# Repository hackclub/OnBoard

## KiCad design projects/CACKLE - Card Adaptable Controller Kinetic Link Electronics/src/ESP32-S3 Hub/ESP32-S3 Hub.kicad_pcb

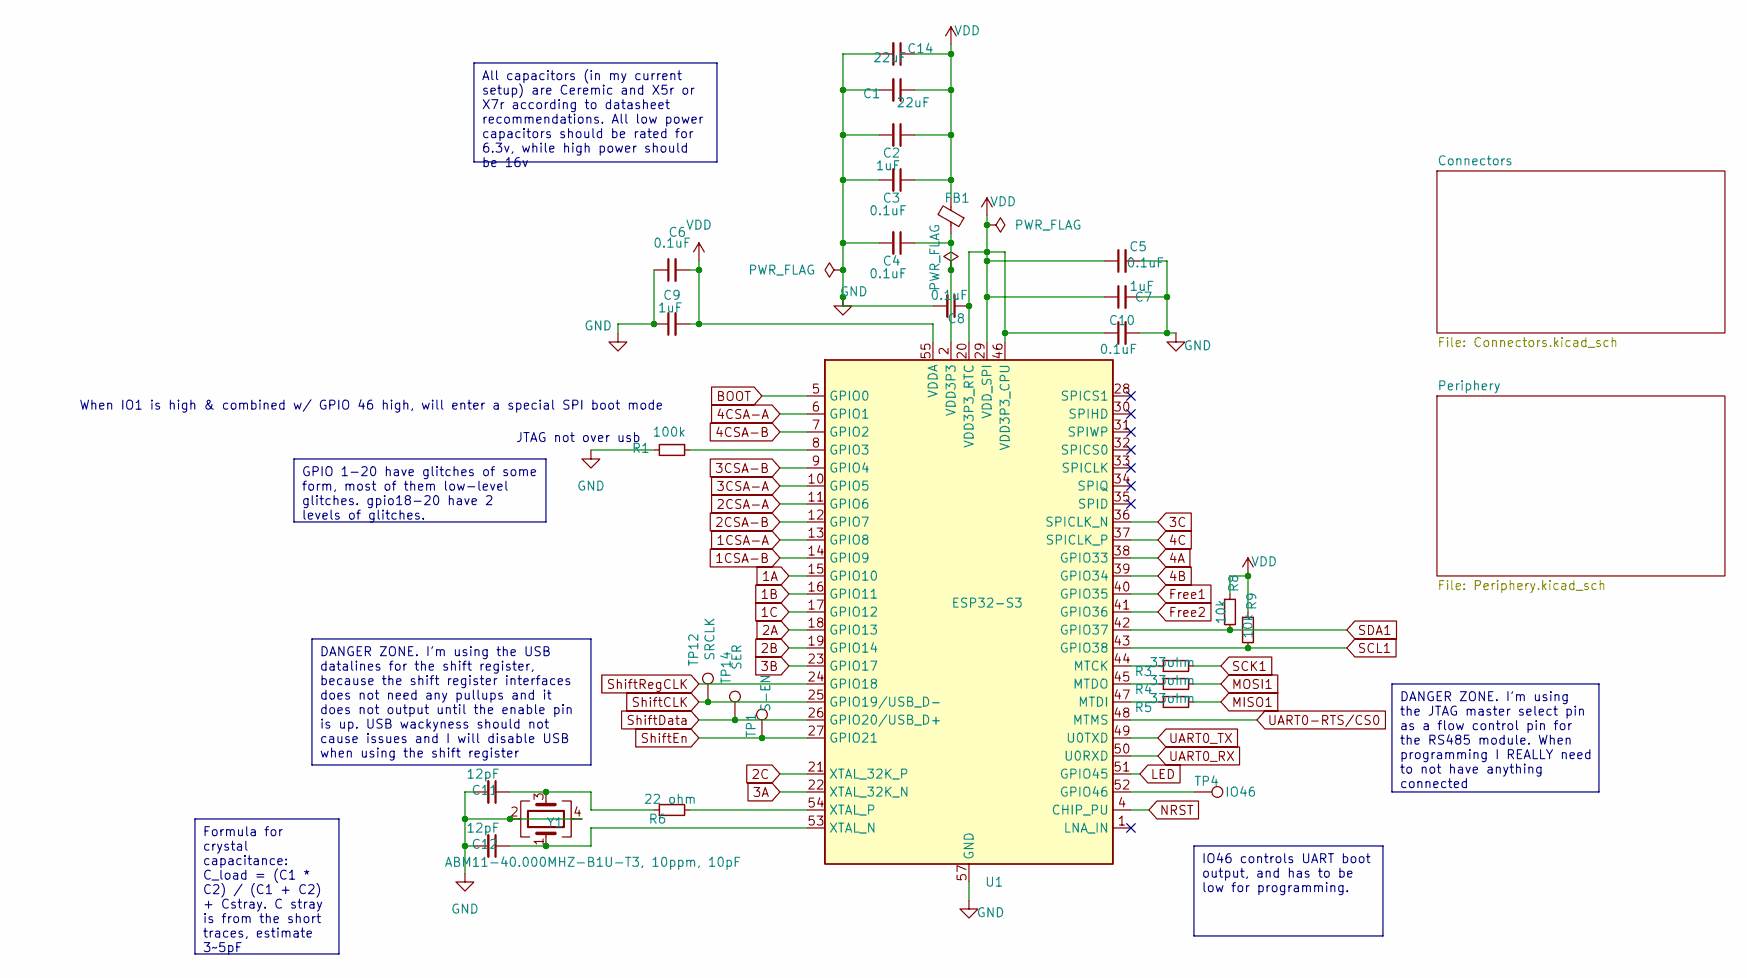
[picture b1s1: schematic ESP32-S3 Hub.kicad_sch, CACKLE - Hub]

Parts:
C1, C14: 22uF; C_0402_1005Metric; LCSC C415703
C2, C7, C9: 1uF; C_0402_1005Metric; LCSC C52923
C3, C4, C5, C6, C8, C10: 0.1uF; C_0402_1005Metric; LCSC C1525
C11, C12: 12pF; C_0402_1005Metric; LCSC C1547
FB1: 120ohm imp @100mhz, 1 amp; L_0402_1005Metric; LCSC C82861
R1: 100k; R_0402_1005Metric; LCSC C25741
R3, R4, R5: 33ohm; R_0402_1005Metric; LCSC C25105
R6: 22 ohm; R_0402_1005Metric; LCSC C25092
R8, R9: 10k; R_0402_1005Metric; LCSC C25744
TP1: S-EN; TestPoint_Pad_D1.0mm
TP4: IO46; TestPoint_Pad_D1.0mm
TP12: SRCLK; TestPoint_Pad_D1.0mm
TP14: SER; TestPoint_Pad_D1.0mm
U1: ESP32-S3; QFN-56-1EP_7x7mm_P0.4mm_EP4x4mm; LCSC C3013940
Y1: ABM11-40.000MHZ-B1U-T3, 10ppm, 10pF; Crystal_SMD_2016-4Pin_2.0x1.6mm; LCSC C648973

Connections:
1A: U1.15 (GPIO10); also elsewhere on the board
1B: U1.16 (GPIO11); also elsewhere on the board
1C: U1.17 (GPIO12); also elsewhere on the board
1CSA-A: U1.13 (GPIO8); also elsewhere on the board
1CSA-B: U1.14 (GPIO9); also elsewhere on the board
2A: U1.18 (GPIO13); also elsewhere on the board
2B: U1.19 (GPIO14); also elsewhere on the board
2C: U1.21 (XTAL_32K_P); also elsewhere on the board
2CSA-A: U1.11 (GPIO6); also elsewhere on the board
2CSA-B: U1.12 (GPIO7); also elsewhere on the board
3A: U1.22 (XTAL_32K_N); also elsewhere on the board
3B: U1.23 (GPIO17); also elsewhere on the board
3C: U1.36 (SPICLK_N); also elsewhere on the board
3CSA-A: U1.10 (GPIO5); also elsewhere on the board
3CSA-B: U1.9 (GPIO4); also elsewhere on the board
4A: U1.38 (GPIO33); also elsewhere on the board
4B: U1.39 (GPIO34); also elsewhere on the board
4C: U1.37 (SPICLK_P); also elsewhere on the board
4CSA-A: U1.6 (GPIO1); also elsewhere on the board
4CSA-B: U1.7 (GPIO2); also elsewhere on the board
BOOT: U1.5 (GPIO0); also elsewhere on the board
Free1: U1.40 (GPIO35); also elsewhere on the board
Free2: U1.41 (GPIO36); also elsewhere on the board
GND: C1.2, C2.2, C3.2, C4.2, C5.2, C6.1, C7.2, C8.2, C9.1, C10.2, C11.2, C12.2, C14.2, R1.2, U1.57 (GND), Y1.2, Y1.4; also elsewhere on the board
LED: U1.51 (GPIO45); also elsewhere on the board
MISO1: R5.2; also elsewhere on the board
MOSI1: R4.2; also elsewhere on the board
NRST: U1.4 (CHIP_PU); also elsewhere on the board
unnamed: C4.1, FB1.1, U1.2 (VDD3P3), U1.3 (VDD3P3)
unnamed: C11.1, R6.1, Y1.3
unnamed: R1.1, U1.8 (GPIO3)
unnamed: TP4.1, U1.52 (GPIO46)
unnamed: R3.1, U1.44 (MTCK)
unnamed: R5.1, U1.47 (MTDI)
unnamed: R4.1, U1.45 (MTDO)
unnamed: C12.1, U1.53 (XTAL_N), Y1.1
unnamed: R6.2, U1.54 (XTAL_P)
SCK1: R3.2; also elsewhere on the board
SCL1: R9.2, U1.43 (GPIO38); also elsewhere on the board
SDA1: R8.2, U1.42 (GPIO37); also elsewhere on the board
ShiftCLK: TP12.1, U1.25 (GPIO19/USB_D-); also elsewhere on the board
ShiftData: TP14.1, U1.26 (GPIO20/USB_D+); also elsewhere on the board
ShiftEn: TP1.1, U1.27 (GPIO21); also elsewhere on the board
ShiftRegCLK: U1.24 (GPIO18); also elsewhere on the board
UART0-RTS/CS0: U1.48 (MTMS); also elsewhere on the board
UART0_RX: U1.50 (U0RXD); also elsewhere on the board
UART0_TX: U1.49 (U0TXD); also elsewhere on the board
VDD: C1.1, C2.1, C3.1, C5.1, C6.2, C7.1, C8.1, C9.2, C10.1, C14.1, FB1.2, R8.1, R9.1, U1.20 (VDD3P3_RTC), U1.29 (VDD_SPI), U1.46 (VDD3P3_CPU), U1.55 (VDDA), U1.56 (VDDA); also elsewhere on the board

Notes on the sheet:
DANGER ZONE. I'm using the JTAG master select pin as a flow control pin for the RS485 module. When programming I REALLY need to not have anything connected
DANGER ZONE. I'm using the USB datalines for the shift register, because the shift register interfaces does not need any pullups and it does not output until the enable pin is up. USB wackyness should not cause issues and I will disable USB when using the shift register
All capacitors (in my current setup) are Ceremic and X5r or X7r according to datasheet recommendations. All low power capacitors should be rated for 6.3v, while high power should be 16v
IO46 controls UART boot output, and has to be low for programming.
GPIO 1-20 have glitches of some form, most of them low-level glitches. gpio18-20 have 2 levels of glitches.
Formula for crystal capacitance: C_load = (C1 * C2) / (C1 + C2) + Cstray. C stray is from the short traces, estimate 3~5pF
JTAG not over usb
When IO1 is high & combined w/ GPIO 46 high, will enter a special SPI boot mode

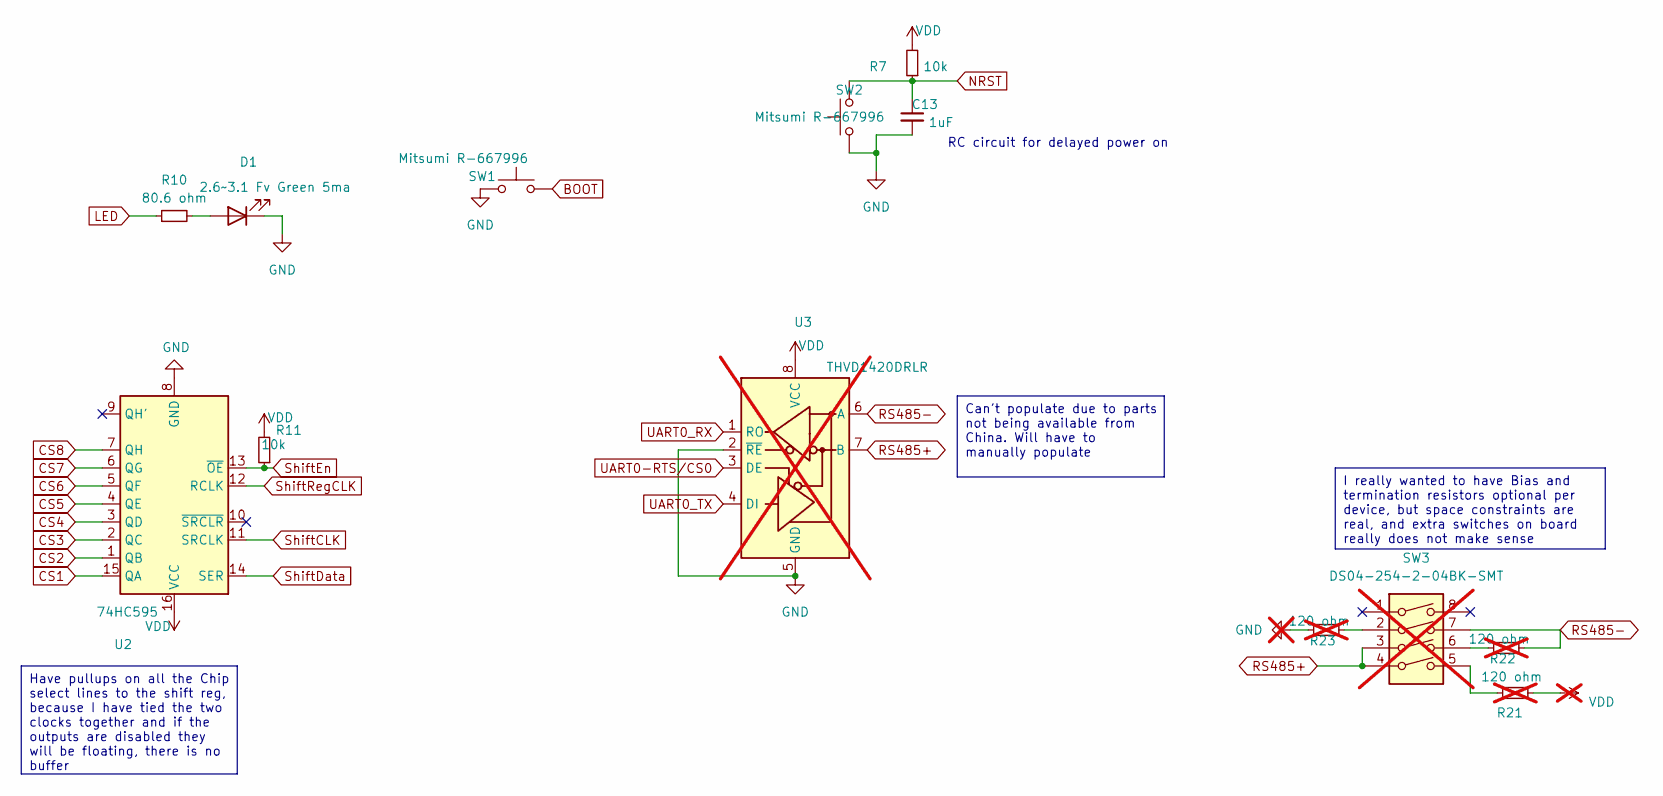
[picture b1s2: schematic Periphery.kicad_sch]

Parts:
C13: 1uF; C_0402_1005Metric; LCSC C52923
D1: 2.6~3.1 Fv Green 5ma; LED_0603_1608Metric_Pad1.05x0.95mm_HandSolder; LCSC C3028858
R7, R11: 10k; R_0402_1005Metric; LCSC C25744
R10: 80.6 ohm; R_0402_1005Metric; LCSC C185392
R21, R22, R23: 120 ohm; R_0402_1005Metric; not fitted
SW1, SW2: Mitsumi R-667996; R-667995_MIT; LCSC C4365007
SW3: DS04-254-2-04BK-SMT; SW_DIP_SPSTx04_Slide_Omron_A6S-410x_W8.9mm_P2.54mm; not fitted
U2: 74HC595; DHVQFN-16-1EP_2.5x3.5mm_P0.5mm_EP1x2mm; LCSC C730243
U3: THVD1420DRLR; SOT-583-8; not fitted

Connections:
BOOT: SW1.2; also elsewhere on the board
CS1: U2.15 (QA); also elsewhere on the board
CS2: U2.1 (QB); also elsewhere on the board
CS3: U2.2 (QC); also elsewhere on the board
CS4: U2.3 (QD); also elsewhere on the board
CS5: U2.4 (QE); also elsewhere on the board
CS6: U2.5 (QF); also elsewhere on the board
CS7: U2.6 (QG); also elsewhere on the board
CS8: U2.7 (QH); also elsewhere on the board
GND: C13.2, D1.1 (K), R23.2, SW1.1, SW2.1, U2.8 (GND), U2.17 (GND), U3.2 (~RE), U3.5 (GND); also elsewhere on the board
LED: R10.1; also elsewhere on the board
NRST: C13.1, R7.1, SW2.2; also elsewhere on the board
unnamed: D1.2 (A), R10.2
unnamed: R21.2, SW3.5
unnamed: R22.2, SW3.6
unnamed: R23.1, SW3.2
RS485+: SW3.3, SW3.4, U3.7 (B); also elsewhere on the board
RS485-: R22.1, SW3.7, U3.6 (A); also elsewhere on the board
ShiftCLK: U2.11 (SRCLK); also elsewhere on the board
ShiftData: U2.14 (SER); also elsewhere on the board
ShiftEn: R11.1, U2.13 (~OE); also elsewhere on the board
ShiftRegCLK: U2.12 (RCLK); also elsewhere on the board
UART0-RTS/CS0: U3.3 (DE); also elsewhere on the board
UART0_RX: U3.1 (RO); also elsewhere on the board
UART0_TX: U3.4 (DI); also elsewhere on the board
VDD: R7.2, R11.2, R21.1, U2.16 (VCC), U3.8 (VCC); also elsewhere on the board

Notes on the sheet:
Can't populate due to parts not being available from China. Will have to manually populate
Have pullups on all the Chip select lines to the shift reg, because I have tied the two clocks together and if the outputs are disabled they will be floating, there is no buffer
I really wanted to have Bias and termination resistors optional per device, but space constraints are real, and extra switches on board really does not make sense
RC circuit for delayed power on

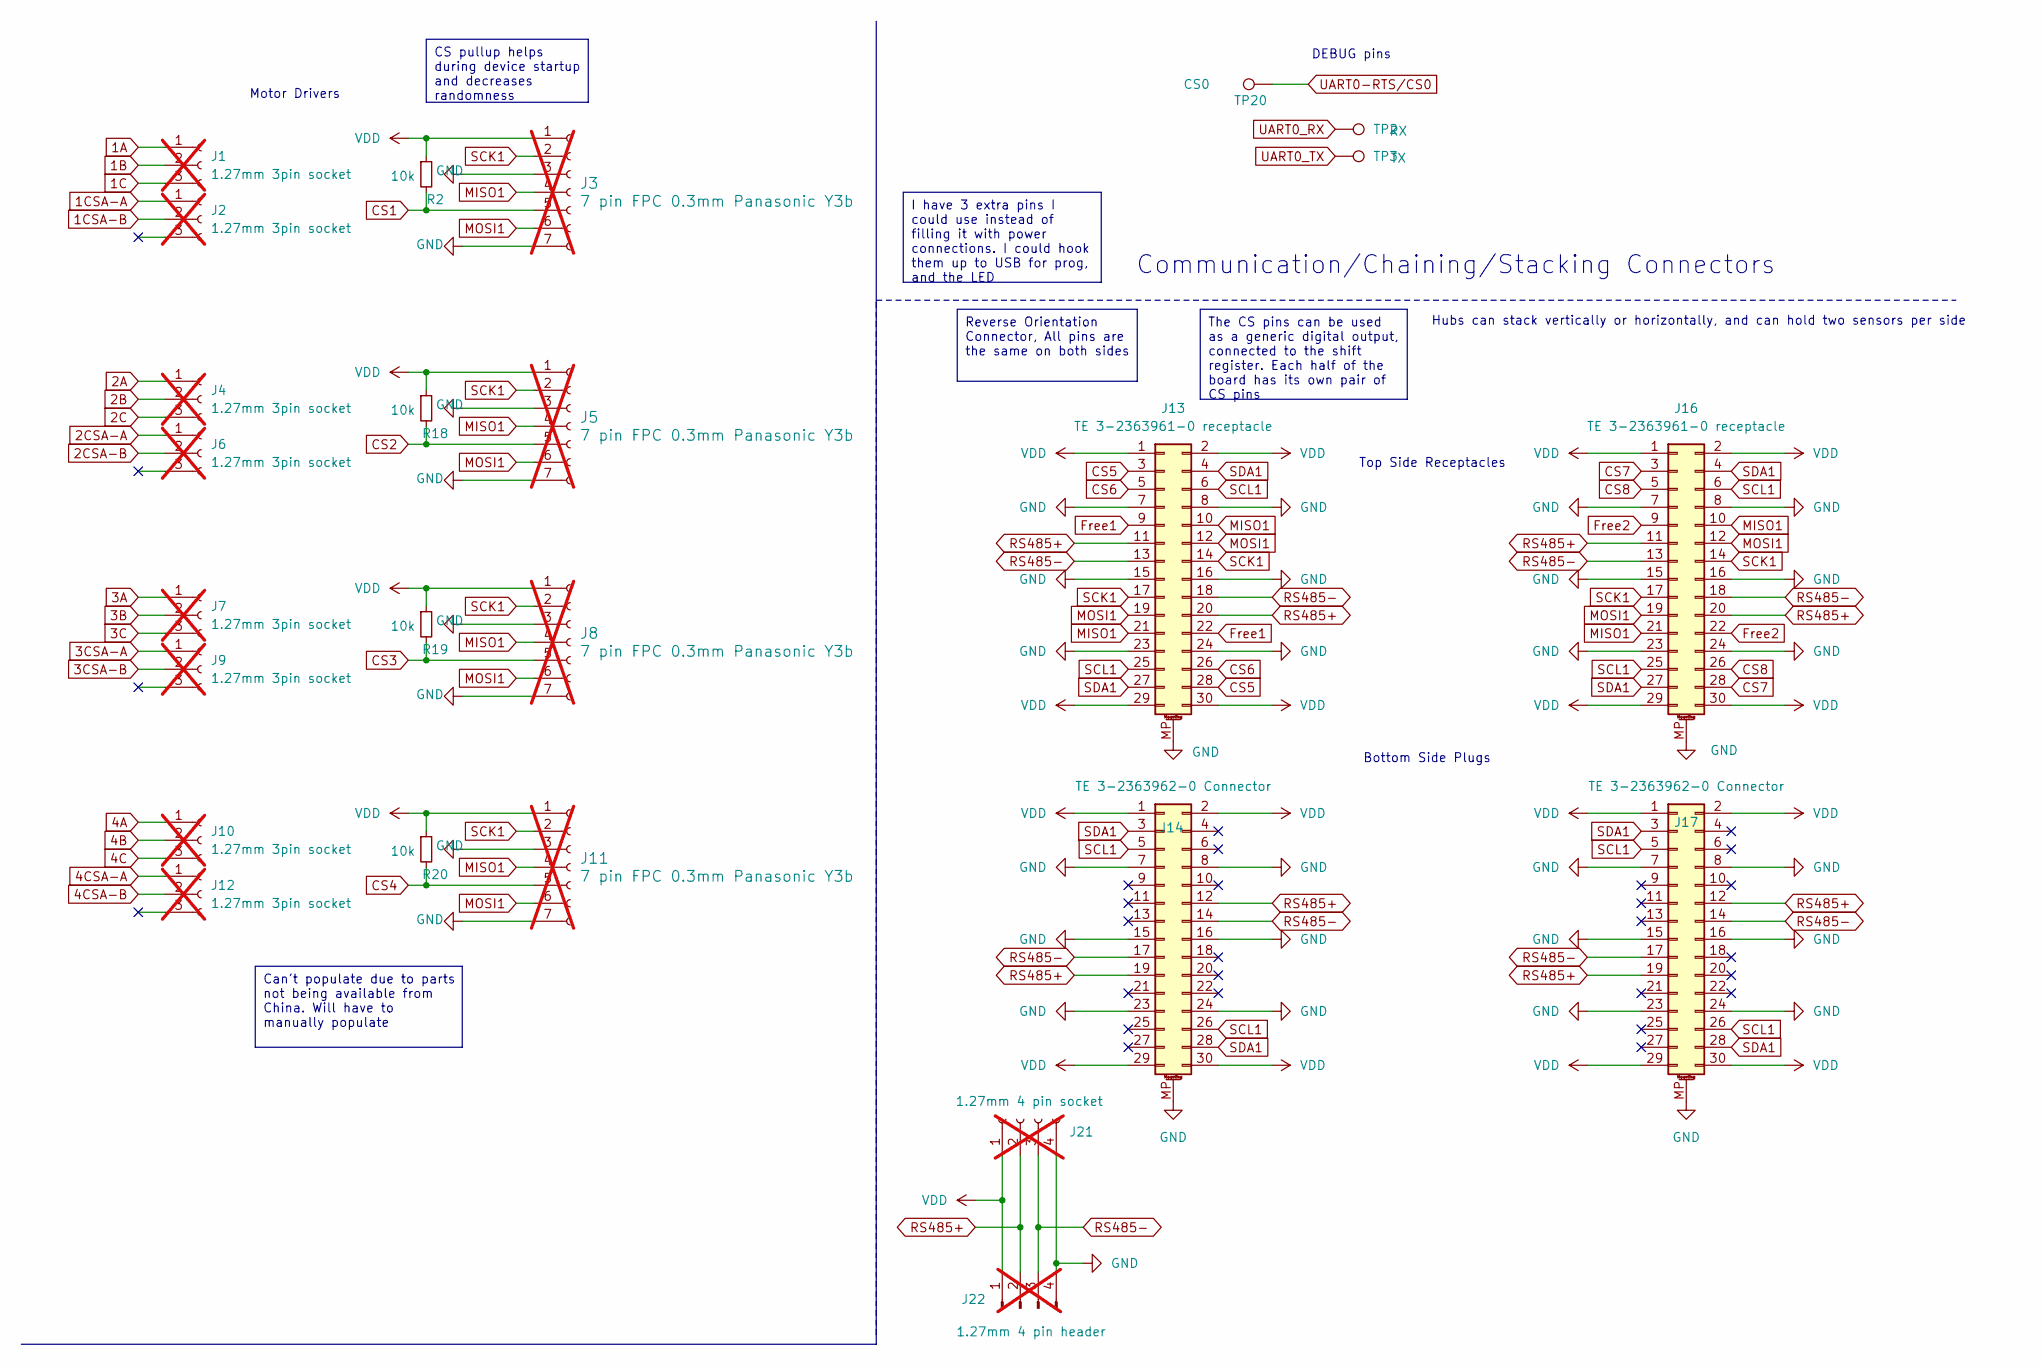
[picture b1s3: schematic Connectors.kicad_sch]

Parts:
J1, J2, J4, J6, J7, J9, J10, J12: 1.27mm 3pin socket; PinHeader_1x03_P1.27mm_Vertical; not fitted
J3, J5, J8, J11: 7 pin FPC 0.3mm Panasonic Y3b; fpc_7pin_0.3mm_connector Panasonic; not fitted
J13, J16: TE 3-2363961-0 receptacle; TE_mezzanine_rec_3-2363961-0; LCSC C425103
J14, J17: TE 3-2363962-0 Connector; TE_mezzanine_conn_3-2363962-0; LCSC C425104
J21: 1.27mm 4 pin socket; PinSocket_1x04_P1.27mm_Vertical; not fitted
J22: 1.27mm 4 pin header; PinHeader_1x04_P1.27mm_Horizontal; not fitted
R2, R18, R19, R20: 10k; R_0402_1005Metric; LCSC C25744
TP2: RX; TestPoint_Pad_D1.0mm
TP3: TX; TestPoint_Pad_D1.0mm
TP20: CS0; TestPoint_Pad_D1.0mm

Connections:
1A: J1.1; also elsewhere on the board
1B: J1.2; also elsewhere on the board
1C: J1.3; also elsewhere on the board
1CSA-A: J2.1; also elsewhere on the board
1CSA-B: J2.2; also elsewhere on the board
2A: J4.1; also elsewhere on the board
2B: J4.2; also elsewhere on the board
2C: J4.3; also elsewhere on the board
2CSA-A: J6.1; also elsewhere on the board
2CSA-B: J6.2; also elsewhere on the board
3A: J7.1; also elsewhere on the board
3B: J7.2; also elsewhere on the board
3C: J7.3; also elsewhere on the board
3CSA-A: J9.1; also elsewhere on the board
3CSA-B: J9.2; also elsewhere on the board
4A: J10.1; also elsewhere on the board
4B: J10.2; also elsewhere on the board
4C: J10.3; also elsewhere on the board
4CSA-A: J12.1; also elsewhere on the board
4CSA-B: J12.2; also elsewhere on the board
CS1: J3.5, R2.2; also elsewhere on the board
CS2: J5.5, R18.2; also elsewhere on the board
CS3: J8.5, R19.2; also elsewhere on the board
CS4: J11.5, R20.2; also elsewhere on the board
CS5: J13.3, J13.28; also elsewhere on the board
CS6: J13.5, J13.26; also elsewhere on the board
CS7: J16.3, J16.28; also elsewhere on the board
CS8: J16.5, J16.26; also elsewhere on the board
Free1: J13.9, J13.22; also elsewhere on the board
Free2: J16.9, J16.22; also elsewhere on the board
GND: J3.3, J3.7, J5.3, J5.7, J8.3, J8.7, J11.3, J11.7, J13.7, J13.8, J13.15, J13.16, J13.23, J13.24, J13.MP (MountPin), J14.7, J14.8, J14.15, J14.16, J14.23, J14.24, J14.MP (MountPin), J16.7, J16.8, J16.15, J16.16, J16.23, J16.24, J16.MP (MountPin), J17.7, J17.8, J17.15, J17.16, J17.23, J17.24, J17.MP (MountPin), J21.4, J22.4; also elsewhere on the board
MISO1: J3.4, J5.4, J8.4, J11.4, J13.10, J13.21, J16.10, J16.21; also elsewhere on the board
MOSI1: J3.6, J5.6, J8.6, J11.6, J13.12, J13.19, J16.12, J16.19; also elsewhere on the board
RS485+: J13.11, J13.20, J14.12, J14.19, J16.11, J16.20, J17.12, J17.19, J21.2, J22.2; also elsewhere on the board
RS485-: J13.13, J13.18, J14.14, J14.17, J16.13, J16.18, J17.14, J17.17, J21.3, J22.3; also elsewhere on the board
SCK1: J3.2, J5.2, J8.2, J11.2, J13.14, J13.17, J16.14, J16.17; also elsewhere on the board
SCL1: J13.6, J13.25, J14.5, J14.26, J16.6, J16.25, J17.5, J17.26; also elsewhere on the board
SDA1: J13.4, J13.27, J14.3, J14.28, J16.4, J16.27, J17.3, J17.28; also elsewhere on the board
UART0-RTS/CS0: TP20.1; also elsewhere on the board
UART0_RX: TP2.1; also elsewhere on the board
UART0_TX: TP3.1; also elsewhere on the board
VDD: J3.1, J5.1, J8.1, J11.1, J13.1, J13.2, J13.29, J13.30, J14.1, J14.2, J14.29, J14.30, J16.1, J16.2, J16.29, J16.30, J17.1, J17.2, J17.29, J17.30, J21.1, J22.1, R2.1, R18.1, R19.1, R20.1; also elsewhere on the board

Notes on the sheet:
Reverse Orientation Connector, All pins are the same on both sides
CS pullup helps during device startup and decreases randomness
Can't populate due to parts not being available from China. Will have to manually populate
The CS pins can be used as a generic digital output, connected to the shift register. Each half of the board has its own pair of CS pins
I have 3 extra pins I could use instead of filling it with power connections. I could hook them up to USB for prog, and the LED
Communication/Chaining/Stacking Connectors
Top Side Receptacles
Motor Drivers
Hubs can stack vertically or horizontally, and can hold two sensors per side
DEBUG pins
Bottom Side Plugs

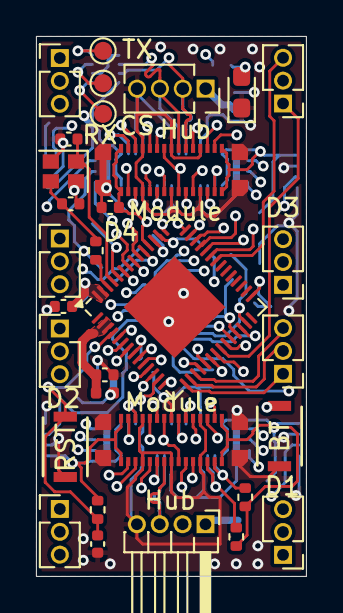
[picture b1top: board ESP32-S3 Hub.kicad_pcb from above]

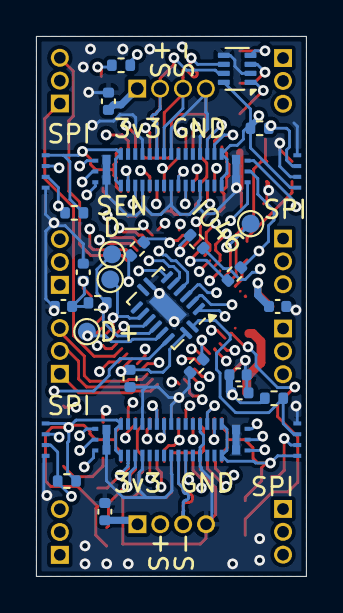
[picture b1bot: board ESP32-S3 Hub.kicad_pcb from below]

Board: 6 copper layers, 15.0 x 30.0 mm, 61 parts (30 on the bottom side), 59 nets.

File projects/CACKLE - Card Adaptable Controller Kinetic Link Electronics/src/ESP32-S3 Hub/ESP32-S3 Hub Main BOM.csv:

"Id";"Designator";"Footprint";"Quantity";"Designation";"Supplier and ref";
1;"D1";"LED_0603_1608Metric_Pad1.05x0.95mm_HandSolder";1;"2.6~3.1 Fv Green 5ma";;;
2;"J22";"PinHeader_1x04_P1.27mm_Horizontal";1;"1.27mm 4 pin header";;;
3;"C13,C9,C2,C7";"C_0402_1005Metric";4;"1uF";;;
4;"C10,C4,C6,C8,C5,C3";"C_0402_1005Metric";6;"0.1uF";;;
5;"R8,R9,R7,R20,R19,R11,R18,R2";"R_0402_1005Metric";8;"10k";;;
6;"J10,J6,J2,J1,J7,J12,J4,J9";"PinHeader_1x03_P1.27mm_Vertical";8;"1.27mm 3pin socket";;;
7;"C12,C11";"C_0402_1005Metric";2;"12pF";;;
8;"SW2,SW1";"R-667995_MIT";2;"Mitsumi R-667996";;;
9;"Y1";"Crystal_SMD_2016-4Pin_2.0x1.6mm";1;"ABM11-40.000MHZ-B1U-T3, 10ppm, 10pF";;;
10;"FB1";"L_0402_1005Metric";1;"120ohm imp @100mhz, 1 amp";;;
11;"U1";"QFN-56-1EP_7x7mm_P0.4mm_EP4x4mm";1;"ESP32-S3";;;
12;"J16,J13";"TE_mezzanine_rec_3-2363961-0";2;"TE 3-2363961-0 receptacle";;;
13;"J21";"PinSocket_1x04_P1.27mm_Vertical";1;"1.27mm 4 pin socket";;;
14;"R6";"R_0402_1005Metric";1;"22 ohm";;;
15;"R1";"R_0402_1005Metric";1;"100k";;;
16;"R10";"R_0402_1005Metric";1;"80.6 ohm";;;
17;"C1,C14";"C_0402_1005Metric";2;"22uF";;;
18;"U2";"DHVQFN-16-1EP_2.5x3.5mm_P0.5mm_EP1x2mm";1;"74HC595";;;
19;"R3,R4,R5";"R_0402_1005Metric";3;"33ohm";;;
20;"J14,J17";"TE_mezzanine_conn_3-2363962-0";2;"TE 3-2363962-0 Connector";;;
21;"J11,J8,J5,J3";"fpc_7pin_0.3mm_connector Panasonic";4;"7 pin FPC 0.3mm Panasonic Y3b";;;
22;"U3";"SOT-583-8";1;"THVD1420DRLR";;;

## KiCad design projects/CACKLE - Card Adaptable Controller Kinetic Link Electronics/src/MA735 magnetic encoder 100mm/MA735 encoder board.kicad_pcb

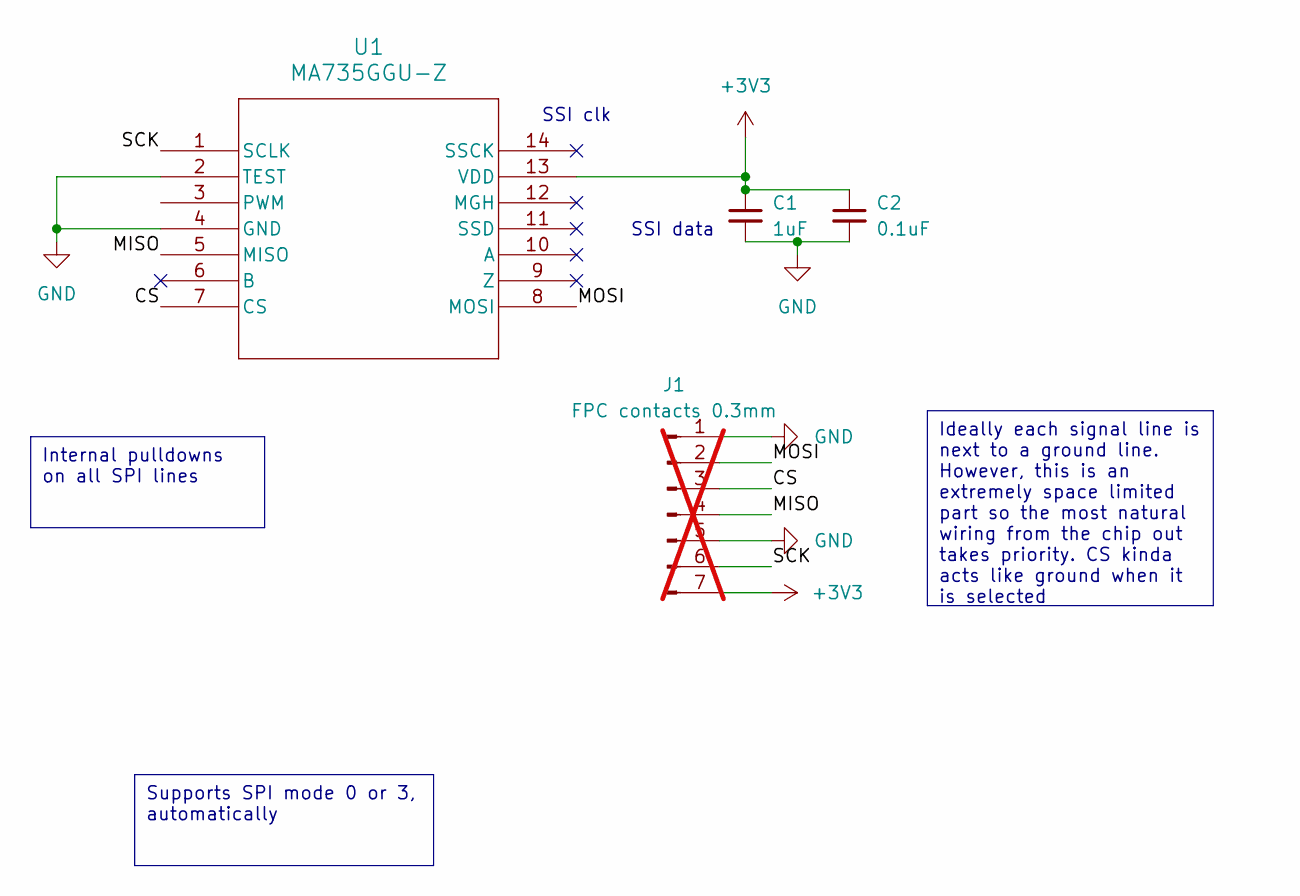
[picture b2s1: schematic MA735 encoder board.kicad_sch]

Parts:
C1: 1uF; C_0402_1005Metric; LCSC C52923
C2: 0.1uF; C_0402_1005Metric; LCSC C1525
J1: FPC contacts 0.3mm; 7pin_fpc_contact_0.3mmptich; not fitted
U1: MA735GGU-Z; UTQFN-14_MA735_MNP; LCSC C17233427

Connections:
+3V3: C1.1, C2.1, J1.7, U1.13 (VDD)
/CS: J1.3, U1.7 (CS)
/MISO: J1.4, U1.5 (MISO)
/MOSI: J1.2, U1.8 (MOSI)
/SCK: J1.6, U1.1 (SCLK)
GND: C1.2, C2.2, J1.1, J1.5, U1.2 (TEST), U1.4 (GND)

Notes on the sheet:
Supports SPI mode 0 or 3, automatically
Ideally each signal line is next to a ground line. However, this is an extremely space limited part so the most natural wiring from the chip out takes priority. CS kinda acts like ground when it is selected
Internal pulldowns on all SPI lines
SSI clk
SSI data

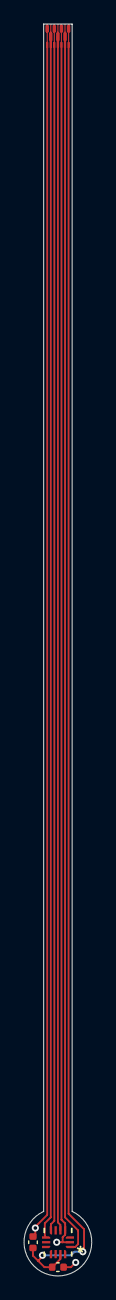
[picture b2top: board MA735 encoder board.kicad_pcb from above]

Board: 2 copper layers, 5.7 x 105.4 mm, 4 parts (0 on the bottom side), 6 nets.

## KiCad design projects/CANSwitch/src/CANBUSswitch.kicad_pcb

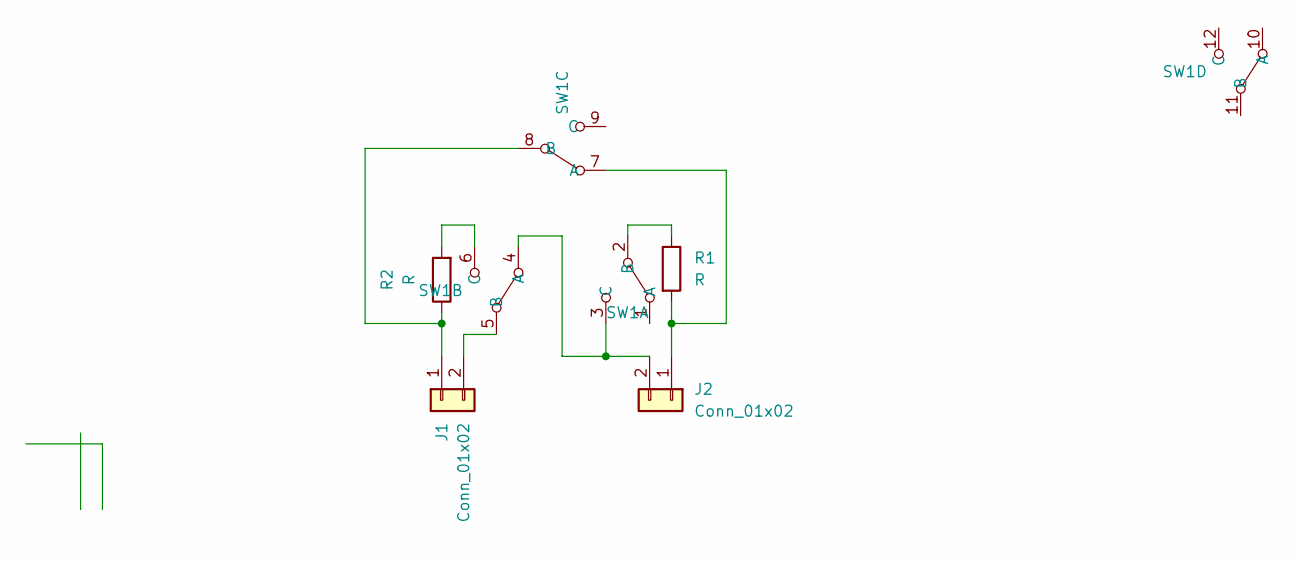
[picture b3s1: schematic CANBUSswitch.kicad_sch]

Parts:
J1, J2: Conn_01x02; WirePad2
R1, R2: R; R_0805_2012Metric
SW1: ★MFS401N−2−Z

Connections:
unnamed: J1.1, R2.1, SW1.8 (B)
unnamed: J1.2, SW1.5 (B)
unnamed: J2.1, R1.2, SW1.7 (A)
unnamed: J2.2, SW1.3 (C), SW1.4 (A)
unnamed: R1.1, SW1.2 (B)
unnamed: R2.2, SW1.6 (C)

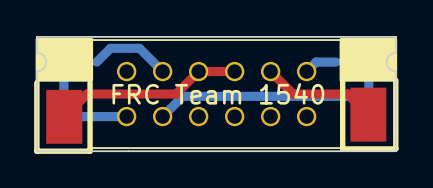
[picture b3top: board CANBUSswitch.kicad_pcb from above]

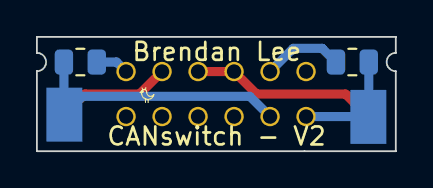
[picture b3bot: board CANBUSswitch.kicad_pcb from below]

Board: 2 copper layers, 19.9 x 6.4 mm, 5 parts (4 on the bottom side), 6 nets.

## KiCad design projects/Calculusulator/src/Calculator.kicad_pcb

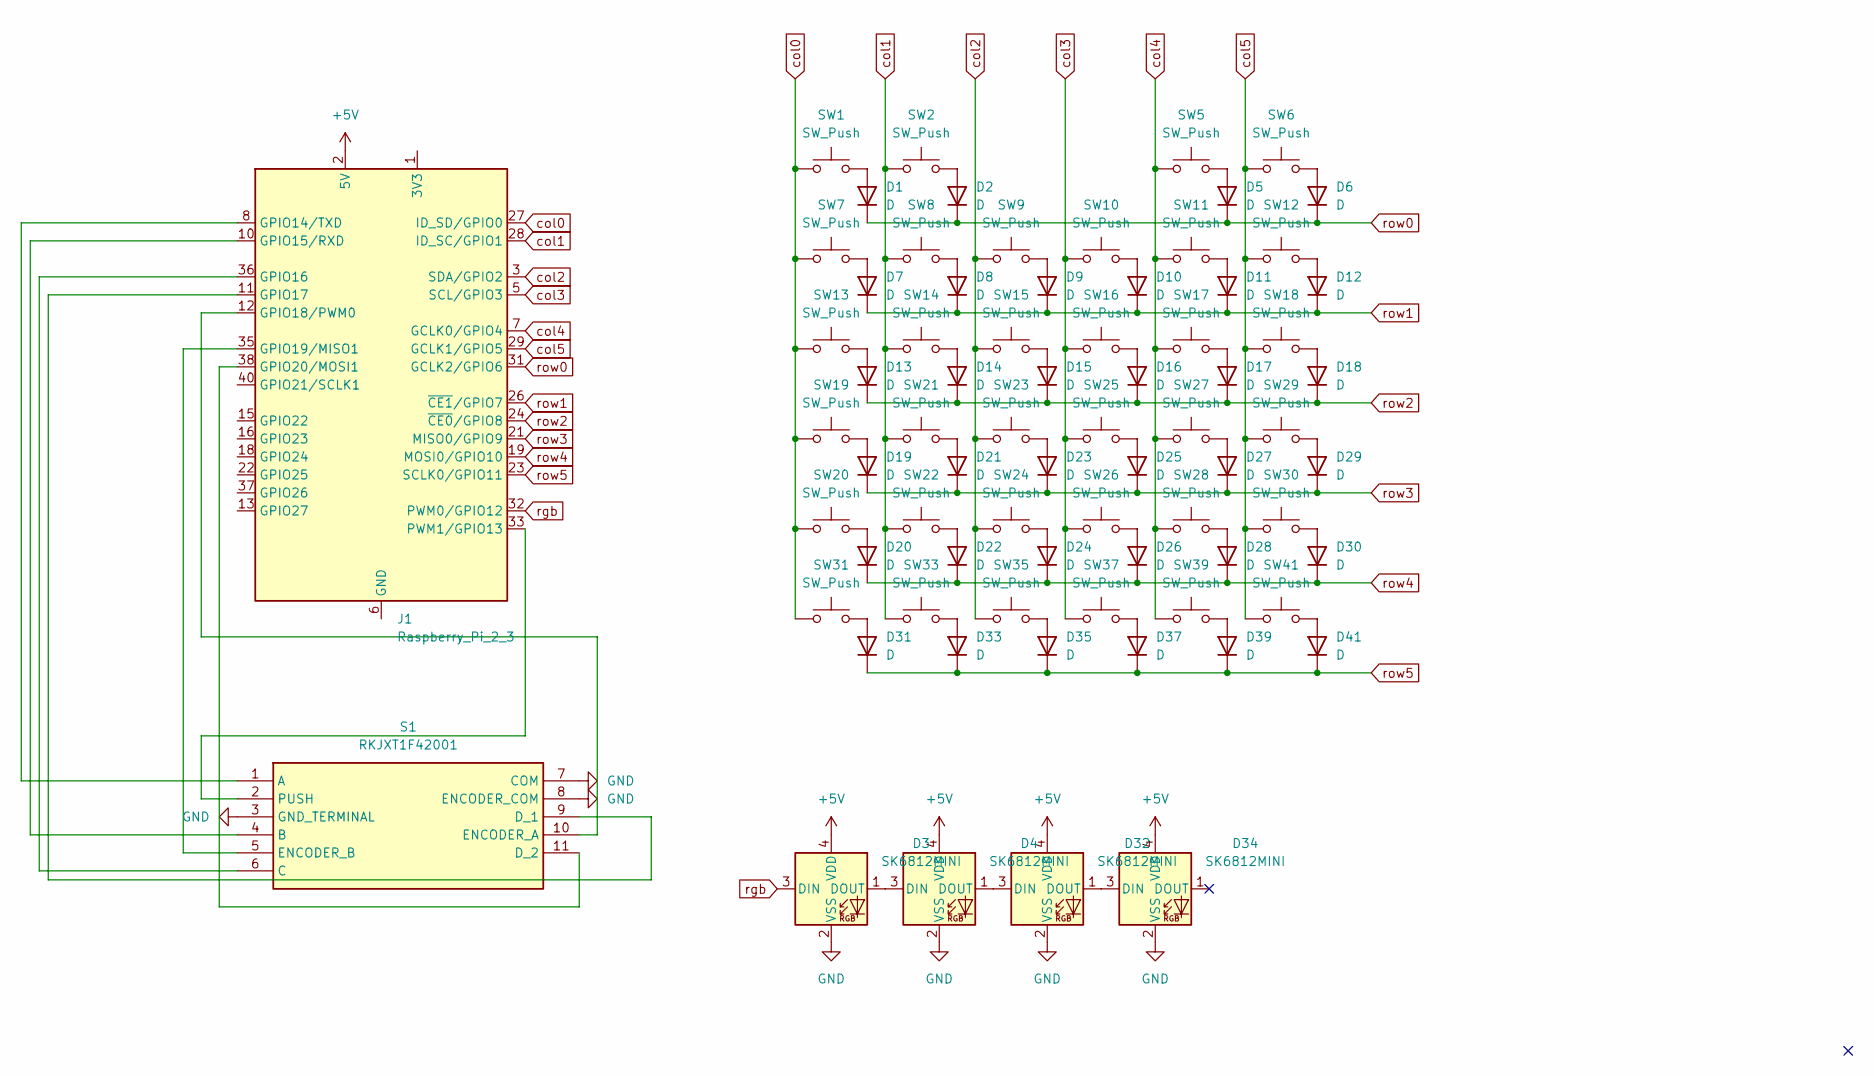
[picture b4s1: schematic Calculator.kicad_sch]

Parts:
D1, D2, D5, D6, D7, D8, D9, D10, D11, D12, D13, D14, D15, D16, D17, D18, D19, D20, D21, D22, D23, D24, D25, D26, D27, D28, D29, D30, D31, D33, D35, D37, D39, D41: D; D_0805_2012Metric_Pad1.15x1.40mm_HandSolder
D3, D4, D32, D34: SK6812MINI; SK6812MINI-E
J1: Raspberry_Pi_2_3; PinHeader_2x20_P2.54mm_Vertical
S1: RKJXT1F42001; Manufacturer_Part_Number RKJXT1F42001; Mouser Part Number 688-RKJXT1F42001
SW1, SW2, SW5, SW6, SW7, SW8, SW9, SW10, SW11, SW12, SW13, SW14, SW15, SW16, SW17, SW18, SW19, SW20, SW21, SW22, SW23, SW24, SW25, SW26, SW27, SW28, SW29, SW30, SW31, SW33, SW35, SW37, SW39, SW41: SW_Push; SW_Cherry_MX_1.00u_PCB

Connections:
+5V: D3.4 (VDD), D4.4 (VDD), D32.4 (VDD), D34.4 (VDD), J1.2 (5V), J1.4 (5V)
GND: D3.2 (VSS), D4.2 (VSS), D32.2 (VSS), D34.2 (VSS), S1.3 (GND_TERMINAL), S1.7 (COM), S1.8 (ENCODER_COM)
unnamed: D1.2 (A), SW1.2
unnamed: D2.2 (A), SW2.2
unnamed: D3.1 (DOUT), D4.3 (DIN)
unnamed: D5.2 (A), SW5.2
unnamed: D6.2 (A), SW6.2
unnamed: D7.2 (A), SW7.2
unnamed: D8.2 (A), SW8.2
unnamed: D9.2 (A), SW9.2
unnamed: D10.2 (A), SW10.2
unnamed: D11.2 (A), SW11.2
unnamed: D12.2 (A), SW12.2
unnamed: D13.2 (A), SW13.2
unnamed: D14.2 (A), SW14.2
unnamed: D15.2 (A), SW15.2
unnamed: D16.2 (A), SW16.2
unnamed: D17.2 (A), SW17.2
unnamed: D18.2 (A), SW18.2
unnamed: D19.2 (A), SW19.2
unnamed: D20.2 (A), SW20.2
unnamed: D21.2 (A), SW21.2
unnamed: D22.2 (A), SW22.2
unnamed: D23.2 (A), SW23.2
unnamed: D24.2 (A), SW24.2
unnamed: D25.2 (A), SW25.2
unnamed: D26.2 (A), SW26.2
unnamed: D27.2 (A), SW27.2
unnamed: D28.2 (A), SW28.2
unnamed: D29.2 (A), SW29.2
unnamed: D30.2 (A), SW30.2
unnamed: D31.2 (A), SW31.2
unnamed: D4.1 (DOUT), D32.3 (DIN)
unnamed: D32.1 (DOUT), D34.3 (DIN)
unnamed: D33.2 (A), SW33.2
unnamed: D35.2 (A), SW35.2
unnamed: D37.2 (A), SW37.2
unnamed: D39.2 (A), SW39.2
unnamed: D41.2 (A), SW41.2
unnamed: J1.1 (3V3), J1.17 (3V3)
unnamed: J1.6 (GND), J1.9 (GND), J1.14 (GND), J1.20 (GND), J1.25 (GND), J1.30 (GND), J1.34 (GND), J1.39 (GND)
unnamed: J1.8 (GPIO14/TXD), S1.1 (A)
unnamed: J1.10 (GPIO15/RXD), S1.4 (B)
unnamed: J1.36 (GPIO16), S1.6 (C)
unnamed: J1.11 (GPIO17), S1.9 (D_1)
unnamed: J1.12 (GPIO18/PWM0), S1.10 (ENCODER_A)
unnamed: J1.35 (GPIO19/MISO1), S1.5 (ENCODER_B)
unnamed: J1.38 (GPIO20/MOSI1), S1.11 (D_2)
unnamed: J1.33 (PWM1/GPIO13), S1.2 (PUSH)
col0: J1.27 (ID_SD/GPIO0), SW1.1, SW7.1, SW13.1, SW19.1, SW20.1, SW31.1
col1: J1.28 (ID_SC/GPIO1), SW2.1, SW8.1, SW14.1, SW21.1, SW22.1, SW33.1
col2: J1.3 (SDA/GPIO2), SW9.1, SW15.1, SW23.1, SW24.1, SW35.1
col3: J1.5 (SCL/GPIO3), SW10.1, SW16.1, SW25.1, SW26.1, SW37.1
col4: J1.7 (GCLK0/GPIO4), SW5.1, SW11.1, SW17.1, SW27.1, SW28.1, SW39.1
col5: J1.29 (GCLK1/GPIO5), SW6.1, SW12.1, SW18.1, SW29.1, SW30.1, SW41.1
rgb: D3.3 (DIN), J1.32 (PWM0/GPIO12)
row0: D1.1 (K), D2.1 (K), D5.1 (K), D6.1 (K), J1.31 (GCLK2/GPIO6)
row1: D7.1 (K), D8.1 (K), D9.1 (K), D10.1 (K), D11.1 (K), D12.1 (K), J1.26 (~CE1/GPIO7)
row2: D13.1 (K), D14.1 (K), D15.1 (K), D16.1 (K), D17.1 (K), D18.1 (K), J1.24 (~CE0/GPIO8)
row3: D19.1 (K), D21.1 (K), D23.1 (K), D25.1 (K), D27.1 (K), D29.1 (K), J1.21 (MISO0/GPIO9)
row4: D20.1 (K), D22.1 (K), D24.1 (K), D26.1 (K), D28.1 (K), D30.1 (K), J1.19 (MOSI0/GPIO10)
row5: D31.1 (K), D33.1 (K), D35.1 (K), D37.1 (K), D39.1 (K), D41.1 (K), J1.23 (SCLK0/GPIO11)

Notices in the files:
projects/CACKLE - Card Adaptable Controller Kinetic Link Electronics/src/ESP32-S3 Hub/Connectors.kicad_sch:
Licensed under CERN-OHL-S v2
